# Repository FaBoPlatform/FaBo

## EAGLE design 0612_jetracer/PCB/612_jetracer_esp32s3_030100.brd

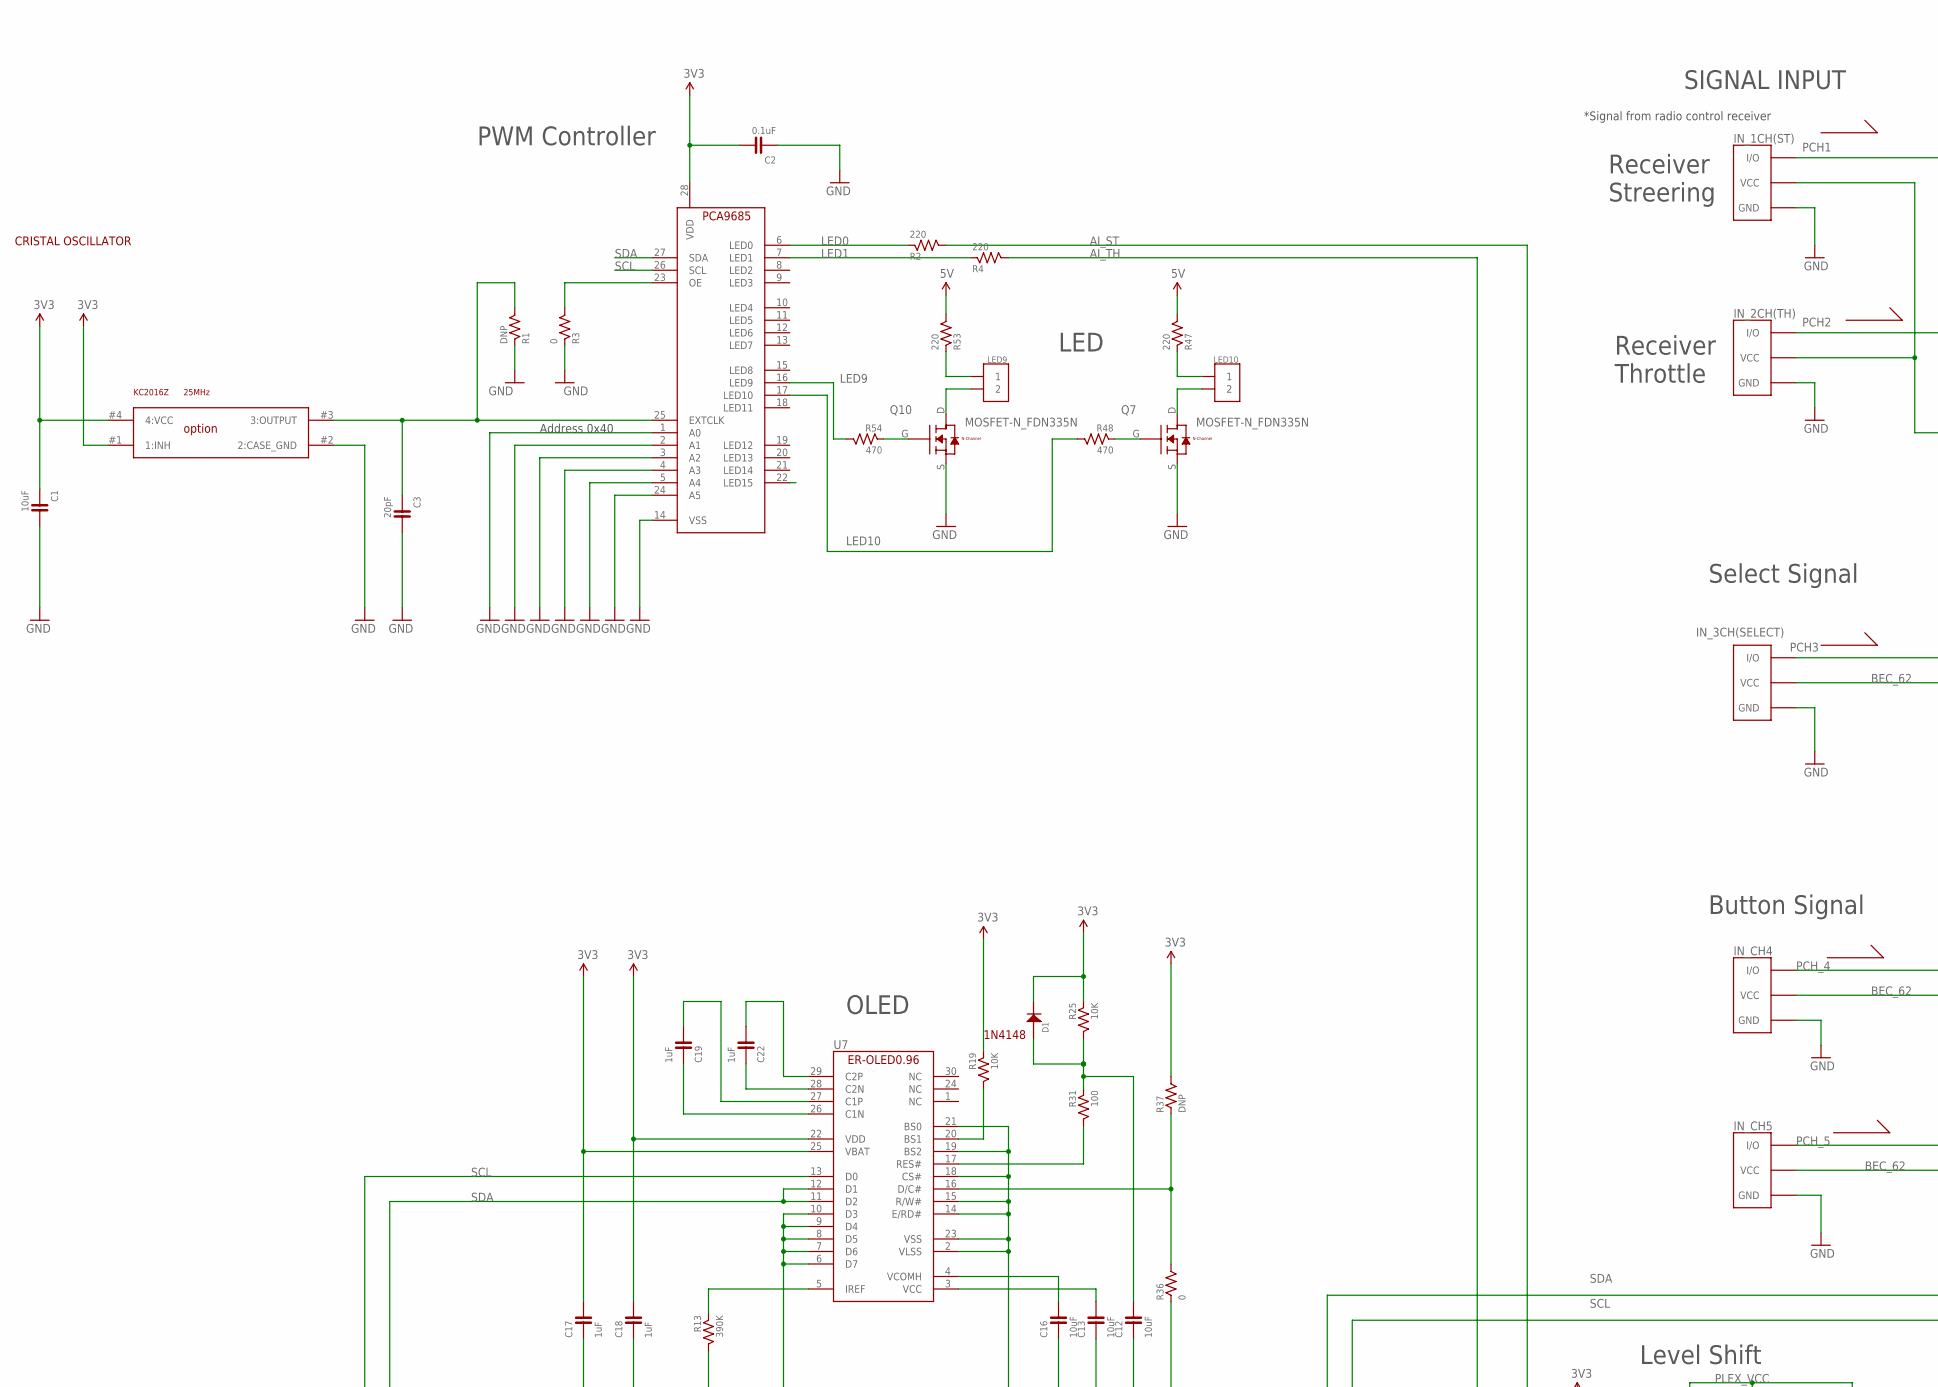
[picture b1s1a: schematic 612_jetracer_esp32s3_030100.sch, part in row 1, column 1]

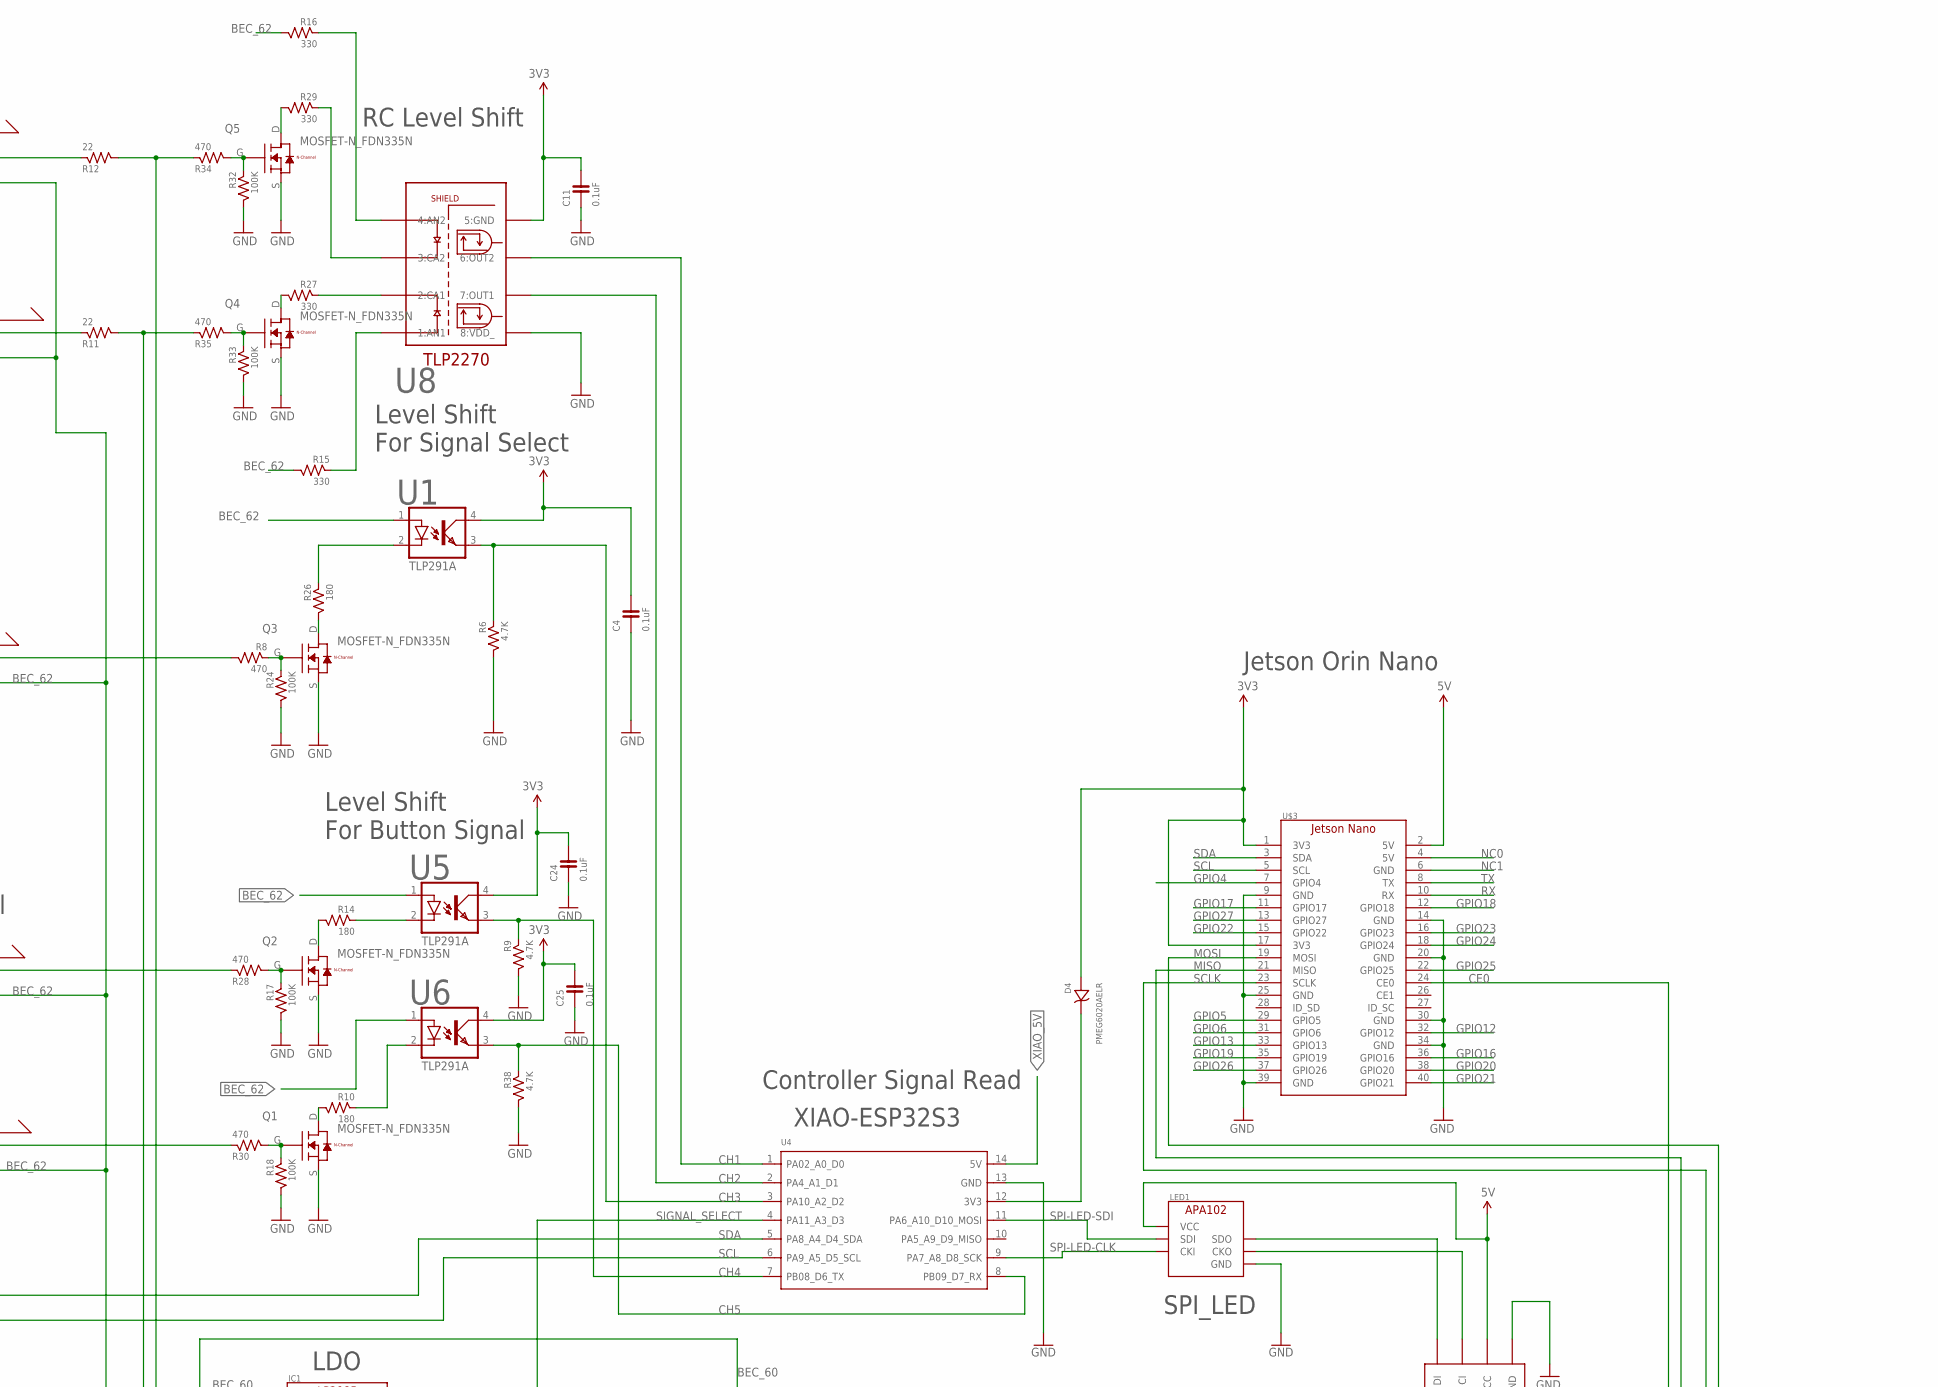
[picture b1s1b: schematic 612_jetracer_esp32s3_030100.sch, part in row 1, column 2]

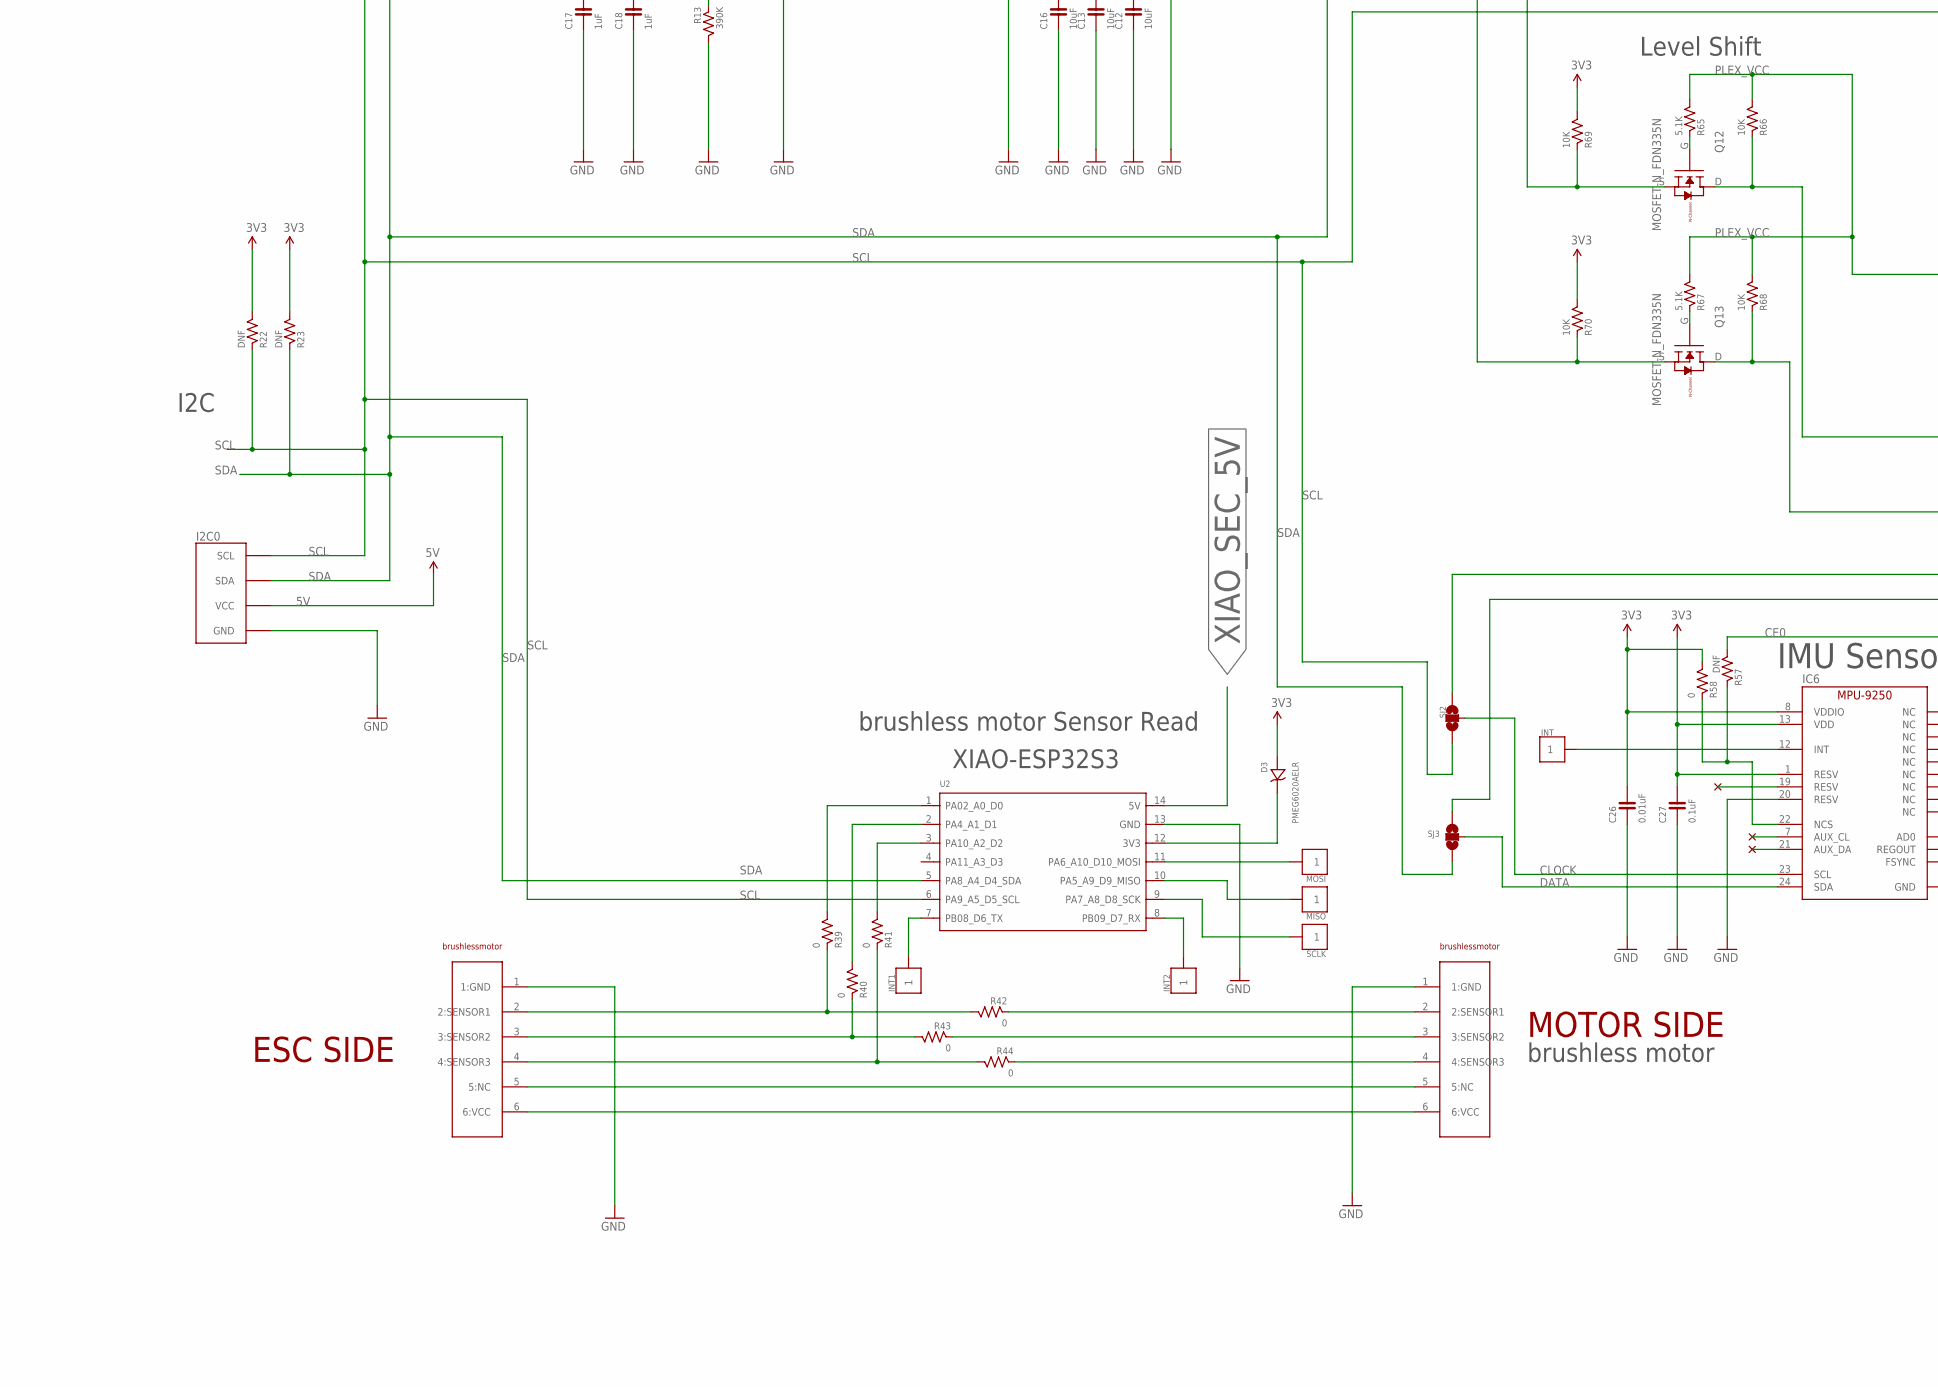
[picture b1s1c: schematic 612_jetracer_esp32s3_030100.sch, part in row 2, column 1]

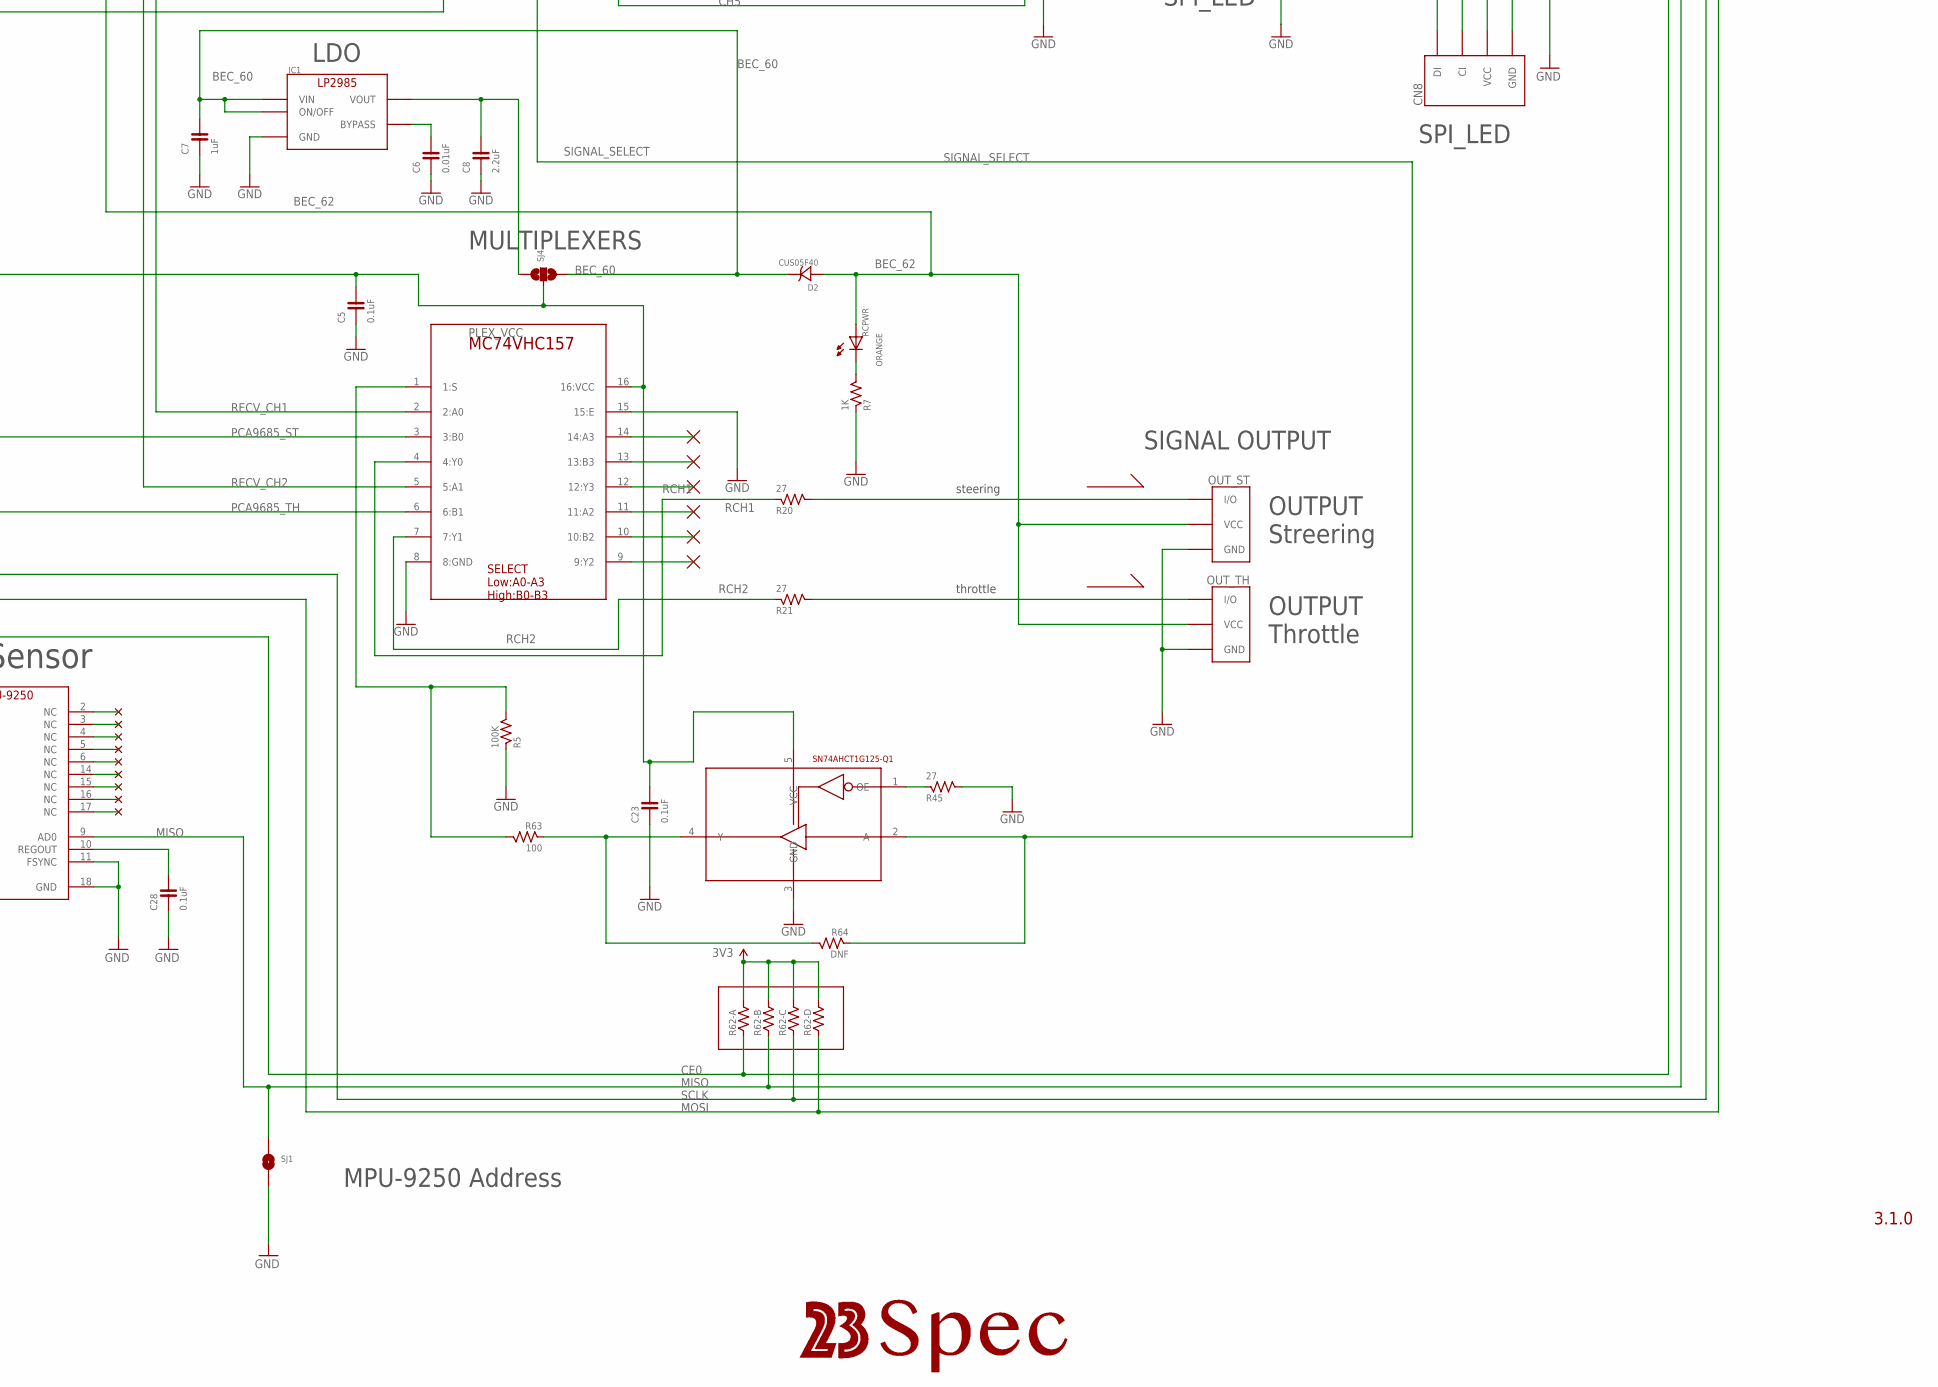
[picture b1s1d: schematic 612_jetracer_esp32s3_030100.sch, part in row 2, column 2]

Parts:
C1, C12, C13, C16: 10uF; 0603
C2, C4, C5, C11, C23, C24, C25, C27, C28: 0.1uF; 0603
C3: 20pF; 0603
C6, C26: 0.01uF; 0603
C7, C17, C18, C19, C22: 1uF; 0603
C8: 2.2uF; 0603
CN8: FABO-SPI-LED-B04B; SPI-B04B-PASK-1
D1: 1N4148; 1N4148W
D2: CUS05F40
D3, D4: PMEG6020AELR; SOD123W
I2C0: FABO_BRICK_I2C-B04B-PASK-1; FABO_BRICK_I2C_B04B-PASK-1
IC1: LP2985-33DBV; SOT-23-5
IC4: PCA9685_BOTTOM
IC6: IS-MPU9250; INVENSENSE-MPU9250
INT, INT1, INT2: PIN_1X1
IN_1CH(ST), IN_2CH(TH), IN_3CH(SELECT): FABO_BRICK_3PIN-HEADER; FABO_BRICK_3PIN_HEADER
IN_CH4, IN_CH5: FABO_BRICK_3PIN-HEADER; FABO_BRICK_3PIN_HEADER
LED1: APA102_IPIXEL; APA102_2020
LED9, LED10: PIN_1X2
MISO: PIN_1X1
MOSI: PIN_1X1
OUT_ST: FABO_BRICK_3PIN-HEADER; FABO_BRICK_3PIN_HEADER
OUT_TH: FABO_BRICK_3PIN-HEADER; FABO_BRICK_3PIN_HEADER
Q1, Q2, Q3, Q4, Q5, Q7, Q10, Q12, Q13: MOSFET-N_FDN335N; SUPERSOT-3
R1: DNP; 0603
R2, R4, R47, R53: 220; 0603
R3, R39, R40, R41, R42, R43, R44, R58: 0; 0603
R5, R17, R18, R24, R32, R33: 100K; 0603
R6, R9, R38: 4.7K; 0603
R7: 1K; 0603
R8, R28, R30, R34, R35, R48, R54: 470; 0603
R10, R14, R26: 180; 0603
R11, R12: 22; 0603
R13: 390K; 0603
R15, R16, R27, R29: 330; 0603
R19, R25, R66, R68, R69, R70: 10K; 0603
R20, R21, R45: 27; 0603
R22, R23, R57, R64: DNF; 0603
R31, R63: 100; 0603
R36: 0; 0805
R37: DNP; 0805
R62: RESISTOR_ARRAY_4; EXBV8V
R65, R67: 5.1K; 0603
RCPWR: ORANGE; 0603
SCLK: PIN_1X1
SJ1: FABO-SMD-JUMPER-SELECT; SMD-JUMPER_SELECT
SJ2, SJ3, SJ4: SMD-JUMPER-3_23SHORT; SMD-JUMPER-3-23SHORT
U1, U5, U6: TLP291A; 11-3C1
U2, U4: MOUDLE-SEEEDUINO-XIAO-ESP32S3-SMD; MOUDLE14P-SMD-2.54-21X17.8MM
U7: ER-OLED0.96-1ER-CON30HT-1; ER-CON30HT-1
U8: TLP2270
U$1: MC74VHC157; MC74VHC157_TSSOP-16
U$3: JETSON_NANOJETSON_ORIN_NANO; JETSON_ORIN_NANO_DIMENTION
U$8: SN74AHCT1G125-Q1; SC70
U$9, U$10: BRUSHLESSMOTOR_CON; B6B-ZR
U$11: KC2016Z

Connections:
3V3: C1.1, C2.2, C4.2, C11.2, C17.2, C18.2, C24.2, C25.2, C26.2, C27.2, D1.CATHODE, D3.2 (ANODE), D4.2 (ANODE), IC4.28 (VDD), IC6.1 (RESV), IC6.8 (VDDIO), IC6.13 (VDD), R19.1, R22.2, R23.2, R25.1, R37.2, R58.2, R62.5 (2), R62.6 (2), R62.7 (2), R62.8 (2), R69.2, R70.2, U1.4 (COL), U5.4 (COL), U6.4 (COL), U7.22 (VDD), U7.25 (VBAT), U8.5 (5:GND), U$3.1 (3V3), U$3.17 (3V3), U$11.#1 (1:INH), U$11.#4 (4:VCC)
5V: CN8.VCC, I2C0.VCC, LED1.VCC, R47.2, R53.2, U$3.2 (5V)
AI_ST: Q12.S, R2.2, R69.1
AI_TH: Q13.S, R4.2, R70.1
BEC_60: C7.2, D2.C (CATHODE), IC1.1 (VIN), IC1.3 (ON/OFF), SJ4.3
BEC_62: D2.A (ANODE), IN_1CH(ST).VCC, IN_2CH(TH).VCC, IN_3CH(SELECT).VCC, IN_CH4.VCC, IN_CH5.VCC, OUT_ST.VCC, OUT_TH.VCC, R15.2, R16.2, RCPWR.ANODE, U1.1 (A), U5.1 (A), U6.1 (A)
CE0: R57.2, R62.1, U$3.24 (CE0)
CH1: U4.1 (PA02_A0_D0), U8.6 (6:OUT2)
CH2: U4.2 (PA4_A1_D1), U8.7 (7:OUT1)
CH3: R6.1, U1.3 (EMI), U4.3 (PA10_A2_D2)
CH4: R9.1, U4.7 (PB08_D6_TX), U5.3 (EMI)
CH5: R38.1, U4.8 (PB09_D7_RX), U6.3 (EMI)
CLOCK: IC6.23 (SCL), SJ2.2
DATA: IC6.24 (SDA), SJ3.2
GND: C1.2, C2.1, C3.2, C4.1, C5.1, C6.1, C7.1, C8.1, C11.1, C12.1, C13.1, C16.1, C17.1, C18.1, C23.1, C24.1, C25.1, C26.1, C27.1, C28.1, CN8.GND, I2C0.GND, IC1.2 (GND), IC4.1 (A0), IC4.2 (A1), IC4.3 (A2), IC4.4 (A3), IC4.5 (A4), IC4.14 (VSS), IC4.24 (A5), IC6.11 (FSYNC), IC6.18 (GND), IC6.20 (RESV), IN_1CH(ST).GND, IN_2CH(TH).GND, IN_3CH(SELECT).GND, IN_CH4.GND, IN_CH5.GND, LED1.GND, OUT_ST.GND, OUT_TH.GND, Q1.S, Q2.S, Q3.S, Q4.S, Q5.S, Q7.S, Q10.S, R1.1, R3.1, R5.1, R6.2, R7.1, R9.2, R13.2, R17.2, R18.2, R24.2, R32.2, R33.2, R36.1, R38.2, R45.2, SJ1.2, U2.13 (GND), U4.13 (GND), U7.2 (VLSS), U7.6 (D7), U7.7 (D6), U7.8 (D5), U7.9 (D4), U7.10 (D3), U7.14 (E/RD#), U7.15 (R/W#), U7.18 (CS#), U7.19 (BS2), U7.21 (BS0), U7.23 (VSS), U8.8 (8:VDD_), U$1.8 (8:GND), U$1.15 (15:E), U$3.9 (GND), U$3.14 (GND), U$3.20 (GND), U$3.25 (GND), U$3.30 (GND), U$3.34 (GND), U$3.39 (GND), U$8.3 (GND), U$9.1 (1:GND), U$10.1 (1:GND), U$11.#2 (2:CASE_GND)
GPIO4: U$3.7 (GPIO4)
GPIO5: U$3.29 (GPIO5)
GPIO6: U$3.31 (GPIO6)
GPIO12: U$3.32 (GPIO12)
GPIO13: U$3.33 (GPIO13)
GPIO16: U$3.36 (GPIO16)
GPIO17: U$3.11 (GPIO17)
GPIO18: U$3.12 (GPIO18)
GPIO19: U$3.35 (GPIO19)
GPIO20: U$3.38 (GPIO20)
GPIO21: U$3.40 (GPIO21)
GPIO22: U$3.15 (GPIO22)
GPIO23: U$3.16 (GPIO23)
GPIO24: U$3.18 (GPIO24)
GPIO25: U$3.22 (GPIO25)
GPIO26: U$3.37 (GPIO26)
GPIO27: U$3.13 (GPIO27)
LED0: IC4.6 (LED0), R2.1
LED1: IC4.7 (LED1), R4.1
LED9: IC4.16 (LED9), R54.2
LED9-D: LED9.2, Q10.D
LED9_G: Q10.G, R54.1
LED10: IC4.17 (LED10), R48.2
LED10-D: LED10.2, Q7.D
LED10-G: Q7.G, R48.1
MISO: IC6.9 (AD0), R62.2 (1), SJ1.1, U$3.21 (MISO)
MOSI: R62.4 (1), SJ3.1, U$3.19 (MOSI)
MOTORCONTROLPOWER: U$9.6 (6:VCC), U$10.6 (6:VCC)
unnamed: IC6.22 (NCS), R57.1, R58.1
unnamed: C22.2, U7.29 (C2P)
unnamed: R5.2, R63.2, U$1.1 (1:S)
unnamed: IC6.12 (INT), INT.1
unnamed: R26.1, U1.2 (C)
unnamed: IC4.23 (OE), R3.2
unnamed: R15.1, U8.1 (1:AN1)
unnamed: R16.1, U8.4 (4:AN2)
unnamed: CN8.DI, LED1.SDO
unnamed: R13.1, U7.5 (IREF)
unnamed: CN8.CI, LED1.CKO
unnamed: C19.2, U7.27 (C1P)
unnamed: C13.2, U7.3 (VCC)
unnamed: R31.2, U7.17 (RES#)
unnamed: R39.1, R42.2, U$9.2 (2:SENSOR1)
unnamed: C19.1, U7.26 (C1N)
unnamed: C22.1, U7.28 (C2N)
unnamed: Q3.G, R8.1, R24.1
unnamed: R7.2, RCPWR.CATHODE
unnamed: C16.2, U7.4 (VCOMH)
unnamed: Q3.D, R26.2
unnamed: Q4.D, R27.2
unnamed: R27.1, U8.2 (2:CA1)
unnamed: Q5.D, R29.2
unnamed: R29.1, U8.3 (3:CA2)
unnamed: R40.1, R43.2, U$9.3 (3:SENSOR2)
unnamed: C12.2, D1.ANODE, R25.2, R31.1
unnamed: Q5.G, R32.1, R34.2
unnamed: D4.1 (CATHODE), U4.12 (3V3)
unnamed: OUT_TH.I/O, R21.2
unnamed: OUT_ST.I/O, R20.2
unnamed: R36.2, R37.1, U7.16 (D/C#)
unnamed: Q4.G, R33.1, R35.2
unnamed: R41.1, R44.2, U$9.4 (4:SENSOR3)
unnamed: C3.1, IC4.25 (EXTCLK), R1.2, U$11.#3 (3:OUTPUT)
unnamed: U$9.5 (5:NC), U$10.5 (5:NC)
unnamed: D3.1 (CATHODE), U2.12 (3V3)
unnamed: Q1.D, R10.2
unnamed: Q2.D, R14.2
unnamed: Q2.G, R17.1, R28.2
unnamed: Q1.G, R18.1, R30.2
unnamed: R19.2, U7.20 (BS1)
unnamed: R14.1, U5.2 (C)
unnamed: R10.1, U6.2 (C)
unnamed: R39.2, U2.1 (PA02_A0_D0)
unnamed: R40.2, U2.2 (PA4_A1_D1)
unnamed: R41.2, U2.3 (PA10_A2_D2)
unnamed: R42.1, U$10.2 (2:SENSOR1)
unnamed: R43.1, U$10.3 (3:SENSOR2)
unnamed: R44.1, U$10.4 (4:SENSOR3)
unnamed: R45.1, U$8.1 (OE)
unnamed: C6.2, IC1.4 (BYPASS)
unnamed: LED10.1, R47.1
unnamed: INT1.1, U2.7 (PB08_D6_TX)
unnamed: INT2.1, U2.8 (PB09_D7_RX)
unnamed: LED9.1, R53.1
unnamed: MOSI.1, U2.11 (PA6_A10_D10_MOSI)
unnamed: MISO.1, U2.10 (PA5_A9_D9_MISO)
unnamed: SCLK.1, U2.9 (PA7_A8_D8_SCK)
unnamed: R63.1, R64.2, U$8.4 (Y)
unnamed: Q12.G, R65.1
unnamed: Q13.G, R67.1
NC0: U$3.4 (5V)
NC1: U$3.6 (GND)
PCA9685_ST: Q12.D, R66.1, U$1.3 (3:B0)
PCA9685_TH: Q13.D, R68.1, U$1.6 (6:B1)
PCH1: IN_1CH(ST).I/O, R12.1
PCH2: IN_2CH(TH).I/O, R11.1
PCH3: IN_3CH(SELECT).I/O, R8.2
PCH_4: IN_CH4.I/O, R28.1
PCH_5: IN_CH5.I/O, R30.1
PLEX_VCC: C5.2, C23.2, R65.2, R66.2, R67.2, R68.2, SJ4.2, U$1.16 (16:VCC), U$8.5 (VCC)
RC3V3: C8.2, IC1.5 (VOUT), SJ4.1
RCH1: R20.1, U$1.4 (4:Y0)
RCH2: R21.1, U$1.7 (7:Y1)
RECV_CH1: R12.2, R34.1, U$1.2 (2:A0)
RECV_CH2: R11.2, R35.1, U$1.5 (5:A1)
REGOUT: C28.2, IC6.10 (REGOUT)
RX: U$3.10 (RX)
SCL: I2C0.SCL, IC4.26 (SCL), R22.1, SJ2.3, U2.6 (PA9_A5_D5_SCL), U4.6 (PA9_A5_D5_SCL), U7.13 (D0), U$3.5 (SCL)
SCLK: R62.3 (1), SJ2.1, U$3.23 (SCLK)
SDA: I2C0.SDA, IC4.27 (SDA), R23.1, SJ3.3, U2.5 (PA8_A4_D4_SDA), U4.5 (PA8_A4_D4_SDA), U7.11 (D2), U7.12 (D1), U$3.3 (SDA)
SIGNAL_SELECT: R64.1, U4.4 (PA11_A3_D3), U$8.2 (A)
SPI-LED-CLK: LED1.CKI, U4.9 (PA7_A8_D8_SCK)
SPI-LED-SDI: LED1.SDI, U4.11 (PA6_A10_D10_MOSI)
TX: U$3.8 (TX)
XIAO_5V: U4.14 (5V)
XIAO_SEC_5V: U2.14 (5V)

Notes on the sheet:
3.1.0
Jetson Orin Nano
PWM Controller
Address 0x40
MULTIPLEXERS
*Signal from radio control receiver
steering
throttle
SIGNAL OUTPUT
SELECT Low:A0-A3 High:B0-B3
option
CRISTAL OSCILLATOR
I2C
1N4148
OLED
SPI_LED
XIAO-ESP32S3
ESC SIDE
MOTOR SIDE
IMU Sensor
brushless motor Sensor Read
RC Level Shift
Level Shift For Signal Select
Level Shift For Button Signal
LED
Controller Signal Read
SIGNAL INPUT
Level Shift
brushless motor
MPU-9250 Address
Button Signal
Select Signal
Receiver Streering
Receiver Throttle
OUTPUT Streering
OUTPUT Throttle
LDO

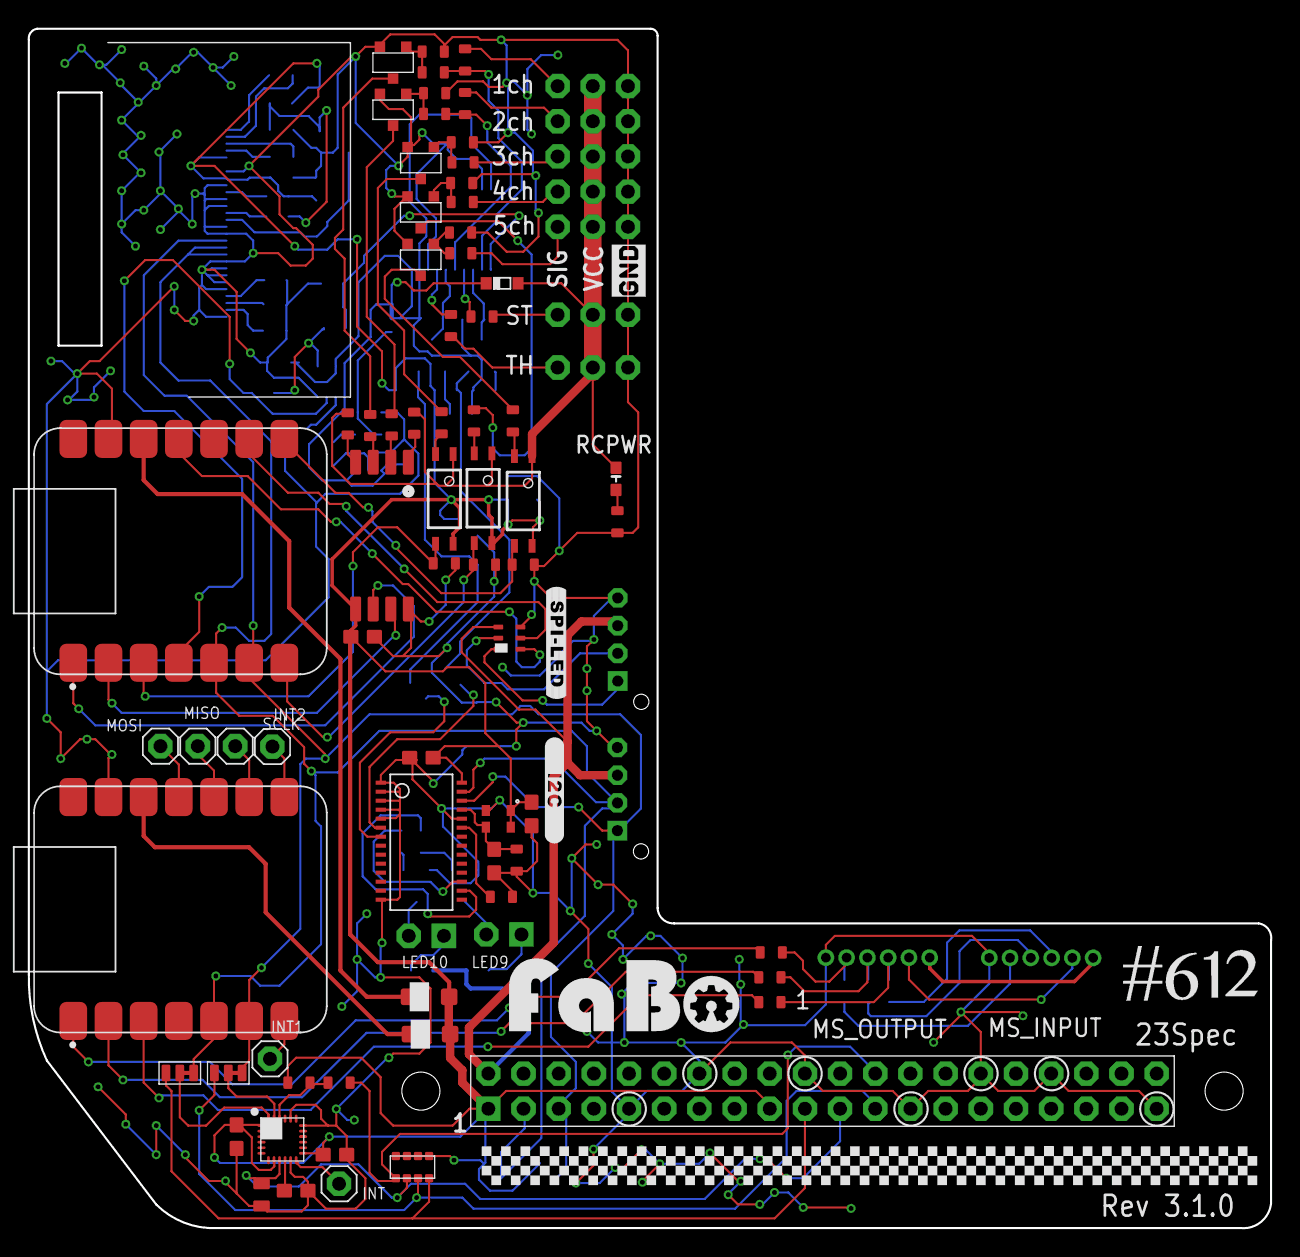
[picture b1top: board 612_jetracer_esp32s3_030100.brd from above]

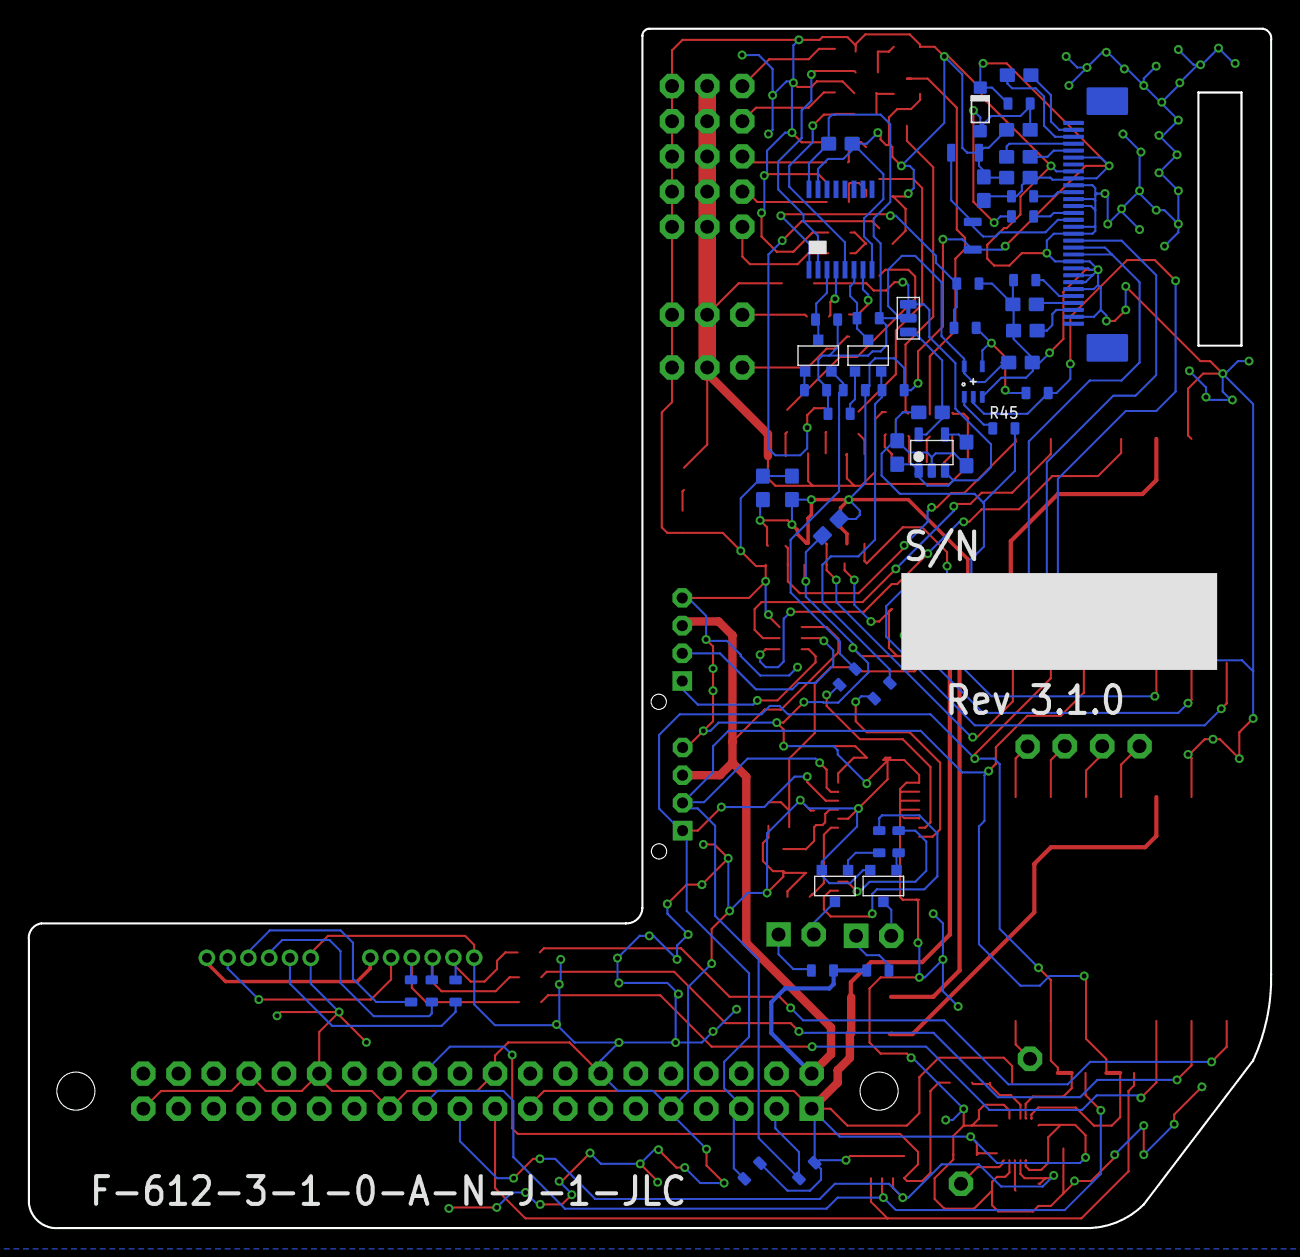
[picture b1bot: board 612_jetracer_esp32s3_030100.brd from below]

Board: 2 copper layers, 89.7 x 86.6 mm, 136 parts (52 on the bottom side), 108 nets.

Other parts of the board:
U$2: LOGO_FABO_L
U$12: LOGO_SILK_GND

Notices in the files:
parts and their libraries:
FaBo-etc: Released under the Creative Commons Attribution-ShareAlike 4.0 License
https://creativecommons.org/licenses/by-sa/4.0
FaBo-etc: Released under the Creative Commons
SparkFun: Licensing: CC v3.0 Share-Alike You are welcome to use this library for commercial purposes.
